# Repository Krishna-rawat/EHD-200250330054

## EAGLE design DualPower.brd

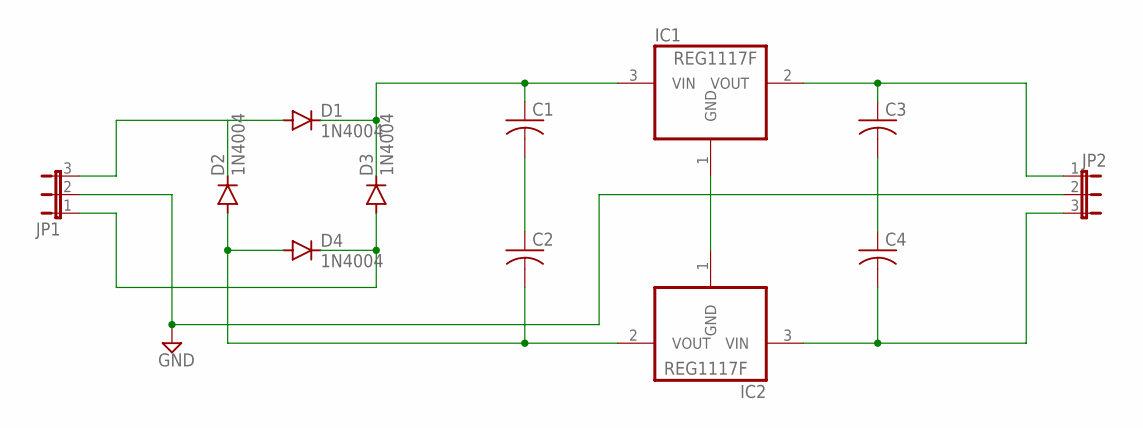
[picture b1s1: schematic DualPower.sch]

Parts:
C1, C2, C3, C4: C-US025-040X050; C025-040X050
D1, D2, D3, D4: 1N4004; DO41-10
IC1, IC2: REG1117F; DD-3
JP1, JP2: JP2E; JP2

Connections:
unnamed: D1.A, D2.C, JP1.3
unnamed: C2.2, D2.A, D4.A, IC2.2 (VOUT)
unnamed: D3.A, D4.C, JP1.1
unnamed: C1.1, D1.C, D3.C, IC1.3 (VIN)
unnamed: C1.2, C2.1
unnamed: IC1.1 (GND), IC2.1 (GND)
unnamed: C3.2, C4.1
unnamed: C3.1, IC1.2 (VOUT), JP2.1
unnamed: C4.2, IC2.3 (VIN), JP2.3
unnamed: JP1.2, JP2.2

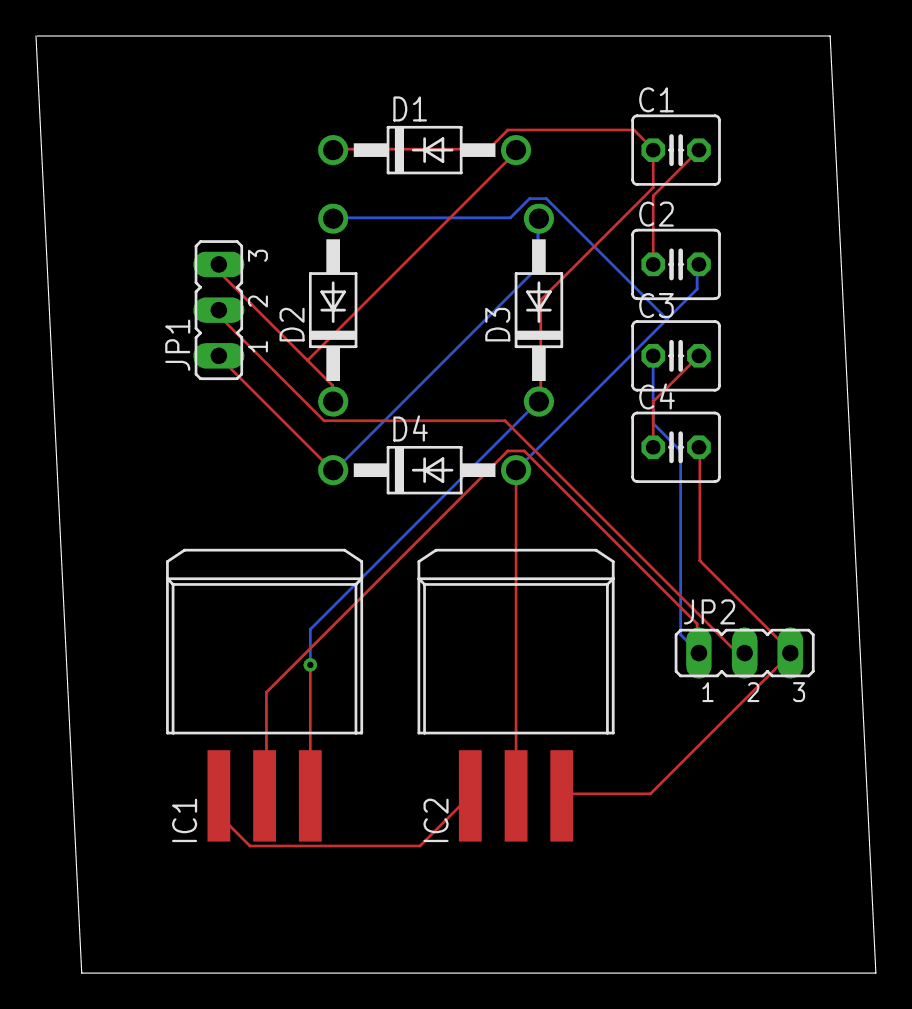
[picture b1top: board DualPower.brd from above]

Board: 2 copper layers, 46.7 x 52.1 mm, 12 parts (0 on the bottom side), 10 nets.

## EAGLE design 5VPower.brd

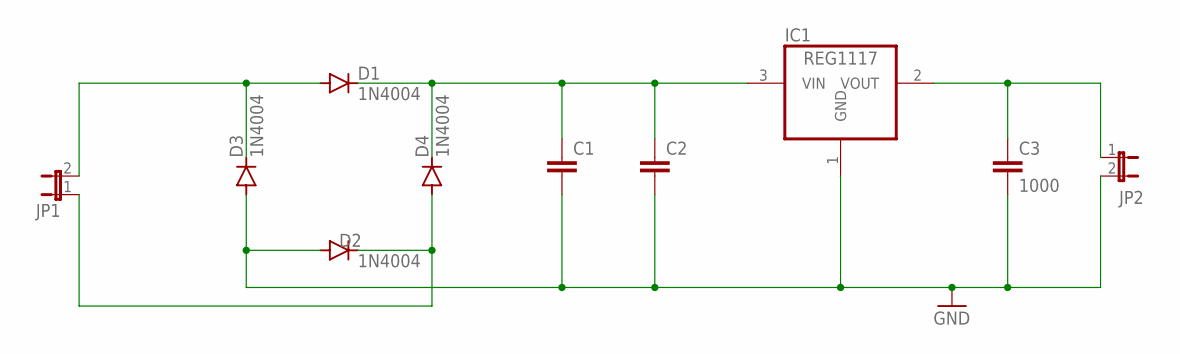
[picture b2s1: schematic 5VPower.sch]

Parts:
C1, C2: C2,5-3; C2.5-3
C3: 1000; C2.5-3
D1, D2, D3, D4: 1N4004; DO41-10
IC1: REG1117; SOT223
JP1, JP2: JP1E; JP1

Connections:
GND: C1.2, C2.2, C3.2, D2.A, D3.A, IC1.1 (GND), JP2.2
unnamed: D1.A, D3.C, JP1.2
unnamed: D2.C, D4.A, JP1.1
unnamed: C1.1, C2.1, D1.C, D4.C, IC1.3 (VIN)
unnamed: C3.1, IC1.2 (VOUT), JP2.1

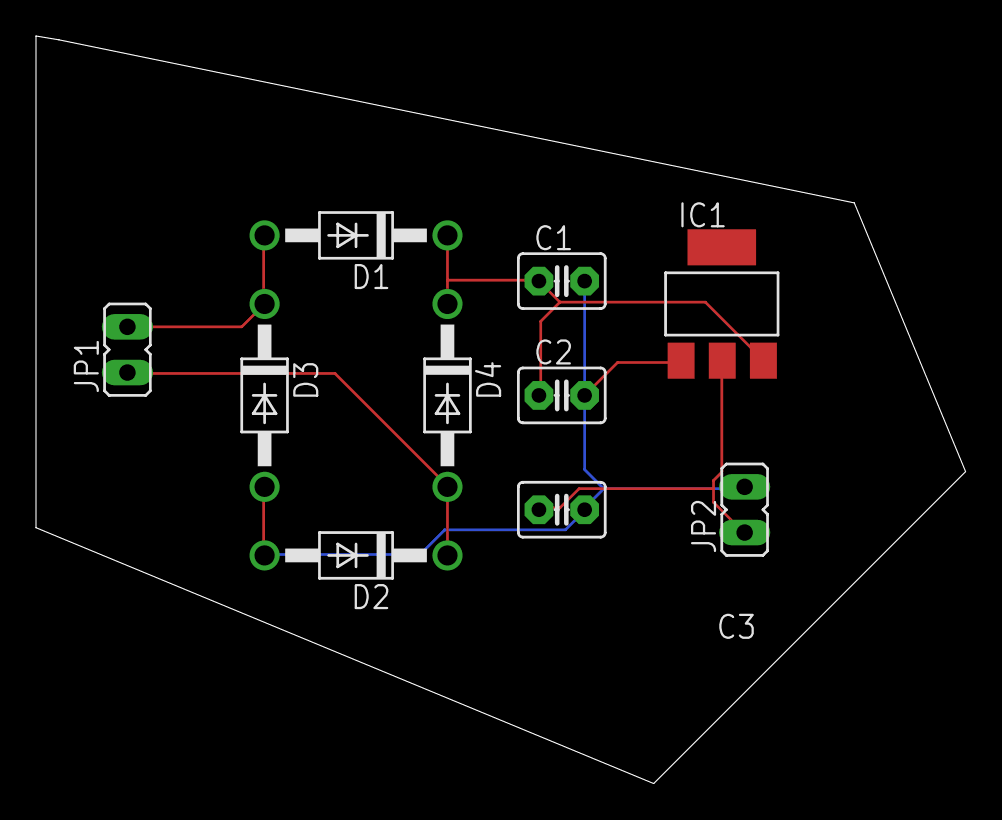
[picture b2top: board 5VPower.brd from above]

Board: 2 copper layers, 51.6 x 41.5 mm, 10 parts (0 on the bottom side), 5 nets.
